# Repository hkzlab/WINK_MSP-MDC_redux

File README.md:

# MSP-MDC Redux

## DISCLAIMER

Any use of this project is **under your own responsibility**.
You will be responsible of checking the correct construction and functionality of your board.
By using this project You will agree that I cannot be held responsible if it will destroy any of your devices, damage your computer, burn down your house or whatever.

## Introduction

Wink is a 1985, breakout-style, arcade game by Midcoin.

The game uses off-the-shelf components for everything, but a bunch of circuitry, called the MSP-MDC module, that acts both as CPU and as 
security (scrambling addresses accessed by the CPU), is placed on 3 sandwiched PCBs encased in epoxy.
This was made to thwart bootleggers, but if something within this epoxied block dies, the whole game stops working.

I painstakingly pulled the block apart and chipped away the epoxy to recover the schematic.

This project contains files to build a compatible board that can be plugged in place of the original MSP-MDC.

## Hardware

The board was designed with [KiCad](https://kicad.org/) EDA.

You can order boards directly from [PCBWay](https://www.pcbway.com/project/shareproject/MSP_MDC_Redux_c4e8a048.html)!

### Bill of Materials

| Component         | Qty | Type / Value                   | Notes                                                    |
| ----------------- | --- | ------------------------------ | -------------------------------------------------------- |
| C1 - C14          | 19  | 100nF / 1206 / ceramic         |                                                          |
| R1, R2            |  2  | 1K / 1206                      |                                                          |
| RN1               |  1  | 9-pin bussed 10K resistor array|                                                          |
|                   |  4  | 4x15pin 2.54mm straight headers| Mount on the 4 sides of the module                       |
| U2                |  1  | DIP-40 Z80A CPU                | It's a good idea to socket this                          |
| U3, U14           |  2  | 74LS374 SO-20                  | 5.3x12.6mm                                               |
| U4                |  1  | 74ALS00 SOIC-14                | 3.9x8.7mm                                                |
| U5                |  1  | 74ALS32 SOIC-14                | 3.9x8.7mm                                                |
| U6                |  1  | 74LS245 SO-20                  | 5.3x12.6mm                                               |
| U7                |  1  | 74ALS244 SO-20                 | 5.3x12.6mm                                               |
| U8, U20           |  2  | 74LS283 SOIC-16                | 3.9x9.9mm                                                |
| U10               |  1  | 74LS00 SOIC-14                 | 3.9x8.7mm                                                |
| U11               |  1  | 74LS32 SOIC-14                 | 3.9x8.7mm                                                |
| U12               |  1  | 74LS86 SOIC-14                 | 3.9x8.7mm                                                |
| U13               |  1  | 74LS166 SOIC-16                | 3.9x9.9mm                                                |
| U15               |  1  | 74LS138 SOIC-16                | 3.9x9.9mm                                                |
| U16 - U19         |  4  | 74LS257 SOIC-16                | 3.9x9.9mm                                                |

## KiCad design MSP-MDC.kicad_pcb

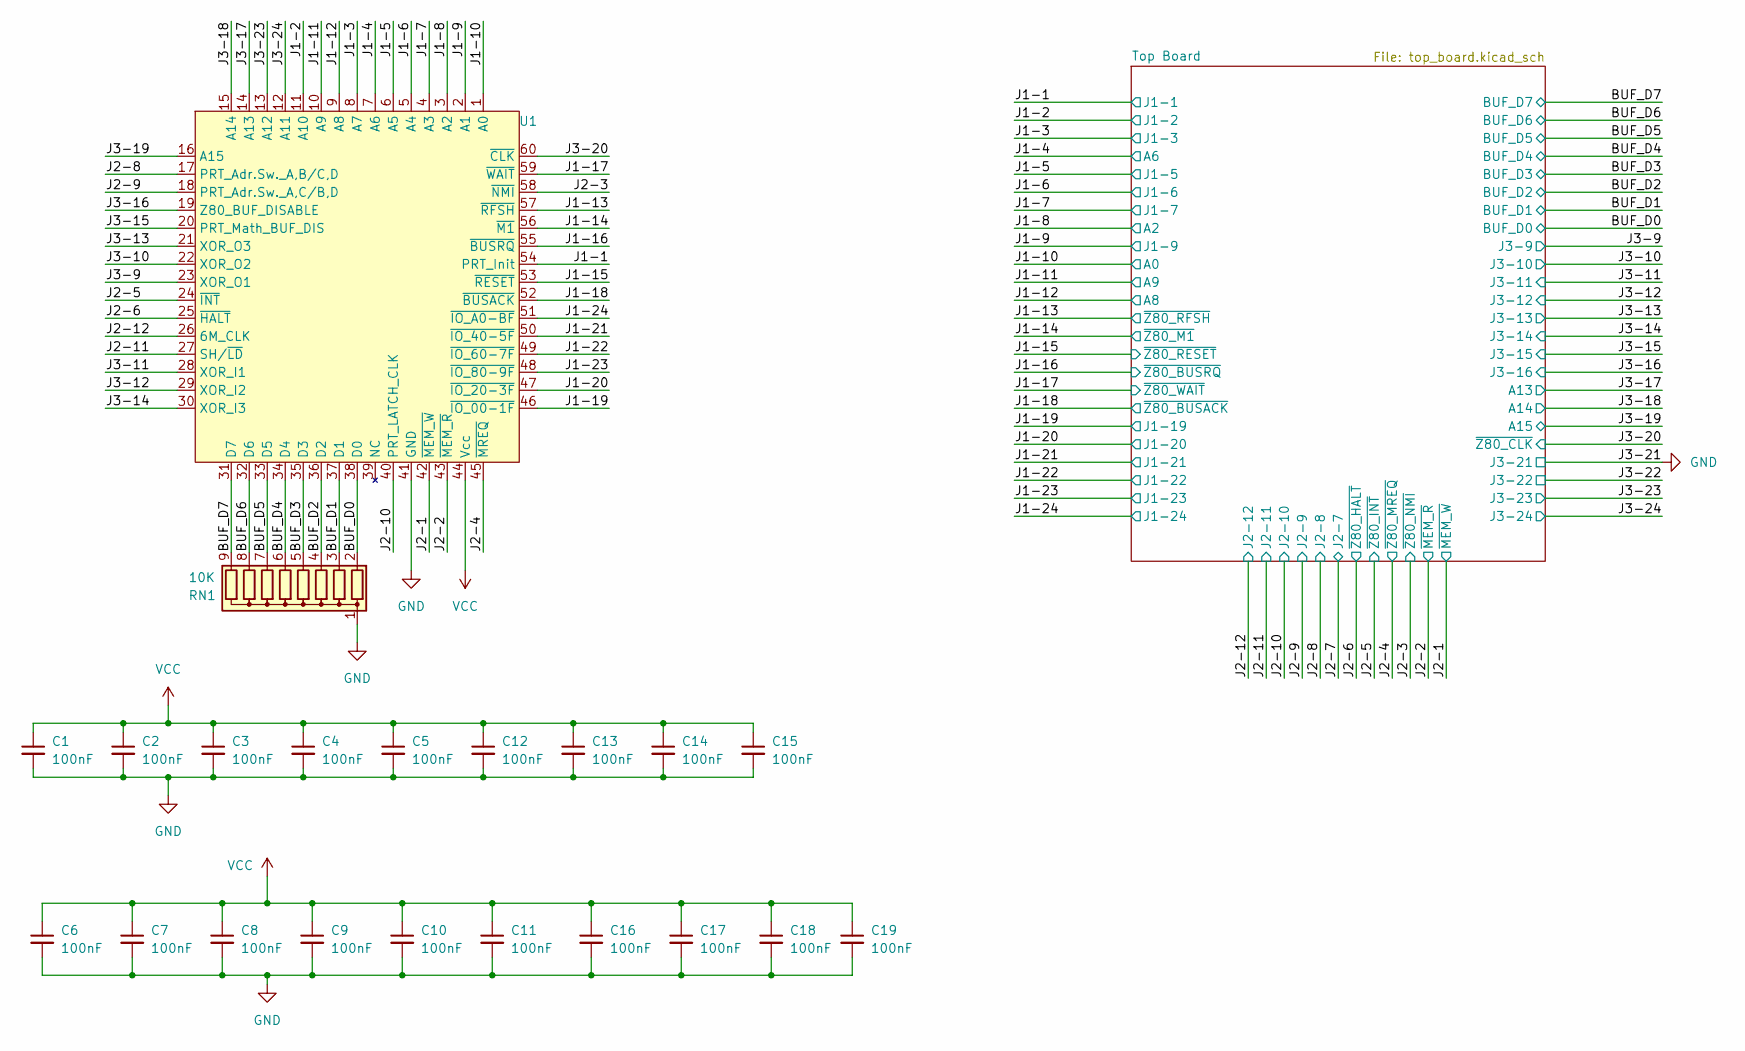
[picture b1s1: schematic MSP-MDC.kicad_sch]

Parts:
C1, C2, C3, C4, C5, C6, C7, C8, C9, C10, C11, C12, C13, C14, C15, C16, C17, C18, C19: 100nF; C_1206_3216Metric_Pad1.33x1.80mm_HandSolder
RN1: 10K; R_Array_SIP9
U1: MSP-MDC

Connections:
/BUF_D0: RN1.2 (R1), U1.38 (D0); also elsewhere on the board
/BUF_D1: RN1.3 (R2), U1.37 (D1); also elsewhere on the board
/BUF_D2: RN1.4 (R3), U1.36 (D2); also elsewhere on the board
/BUF_D3: RN1.5 (R4), U1.35 (D3); also elsewhere on the board
/BUF_D4: RN1.6 (R5), U1.34 (D4); also elsewhere on the board
/BUF_D5: RN1.7 (R6), U1.33 (D5); also elsewhere on the board
/BUF_D6: RN1.8 (R7), U1.32 (D6); also elsewhere on the board
/BUF_D7: RN1.9 (R8), U1.31 (D7); also elsewhere on the board
/J1-1: U1.54 (PRT_Init); also elsewhere on the board
/J1-2: U1.11 (A10); also elsewhere on the board
/J1-3: U1.8 (A7); also elsewhere on the board
/J1-4: U1.7 (A6); also elsewhere on the board
/J1-5: U1.6 (A5); also elsewhere on the board
/J1-6: U1.5 (A4); also elsewhere on the board
/J1-7: U1.4 (A3); also elsewhere on the board
/J1-8: U1.3 (A2); also elsewhere on the board
/J1-9: U1.2 (A1); also elsewhere on the board
/J1-10: U1.1 (A0); also elsewhere on the board
/J1-11: U1.10 (A9); also elsewhere on the board
/J1-12: U1.9 (A8); also elsewhere on the board
/J1-13: U1.57 (~RFSH); also elsewhere on the board
/J1-14: U1.56 (~M1); also elsewhere on the board
/J1-15: U1.53 (~RESET); also elsewhere on the board
/J1-16: U1.55 (~BUSRQ); also elsewhere on the board
/J1-17: U1.59 (~WAIT); also elsewhere on the board
/J1-18: U1.52 (~BUSACK); also elsewhere on the board
/J1-19: U1.46 (~IO_00-1F); also elsewhere on the board
/J1-20: U1.47 (~IO_20-3F); also elsewhere on the board
/J1-21: U1.50 (~IO_40-5F); also elsewhere on the board
/J1-22: U1.49 (~IO_60-7F); also elsewhere on the board
/J1-23: U1.48 (~IO_80-9F); also elsewhere on the board
/J1-24: U1.51 (~IO_A0-BF); also elsewhere on the board
/J2-1: U1.42 (~MEM_W); also elsewhere on the board
/J2-2: U1.43 (~MEM_R); also elsewhere on the board
/J2-3: U1.58 (~NMI); also elsewhere on the board
/J2-4: U1.45 (~MREQ); also elsewhere on the board
/J2-5: U1.24 (~INT); also elsewhere on the board
/J2-6: U1.25 (~HALT); also elsewhere on the board
/J2-8: U1.17 (PRT_Adr.Sw._A,B/C,D); also elsewhere on the board
/J2-9: U1.18 (PRT_Adr.Sw._A,C/B,D); also elsewhere on the board
/J2-10: U1.40 (PRT_LATCH_CLK); also elsewhere on the board
/J2-11: U1.27 (SH/~LD); also elsewhere on the board
/J2-12: U1.26 (6M_CLK); also elsewhere on the board
/J3-9: U1.23 (XOR_O1); also elsewhere on the board
/J3-10: U1.22 (XOR_O2); also elsewhere on the board
/J3-11: U1.28 (XOR_I1); also elsewhere on the board
/J3-12: U1.29 (XOR_I2); also elsewhere on the board
/J3-13: U1.21 (XOR_O3); also elsewhere on the board
/J3-14: U1.30 (XOR_I3); also elsewhere on the board
/J3-15: U1.20 (PRT_Math_BUF_DIS); also elsewhere on the board
/J3-16: U1.19 (Z80_BUF_DISABLE); also elsewhere on the board
/J3-17: U1.14 (A13); also elsewhere on the board
/J3-18: U1.15 (A14); also elsewhere on the board
/J3-19: U1.16 (A15); also elsewhere on the board
/J3-20: U1.60 (~CLK); also elsewhere on the board
/J3-23: U1.13 (A12); also elsewhere on the board
/J3-24: U1.12 (A11); also elsewhere on the board
GND: C1.2, C2.2, C3.2, C4.2, C5.2, C6.2, C7.2, C8.2, C9.2, C10.2, C11.2, C12.2, C13.2, C14.2, C15.2, C16.2, C17.2, C18.2, C19.2, RN1.1 (common), U1.41 (GND); also elsewhere on the board
VCC: C1.1, C2.1, C3.1, C4.1, C5.1, C6.1, C7.1, C8.1, C9.1, C10.1, C11.1, C12.1, C13.1, C14.1, C15.1, C16.1, C17.1, C18.1, C19.1, U1.44 (Vcc); also elsewhere on the board

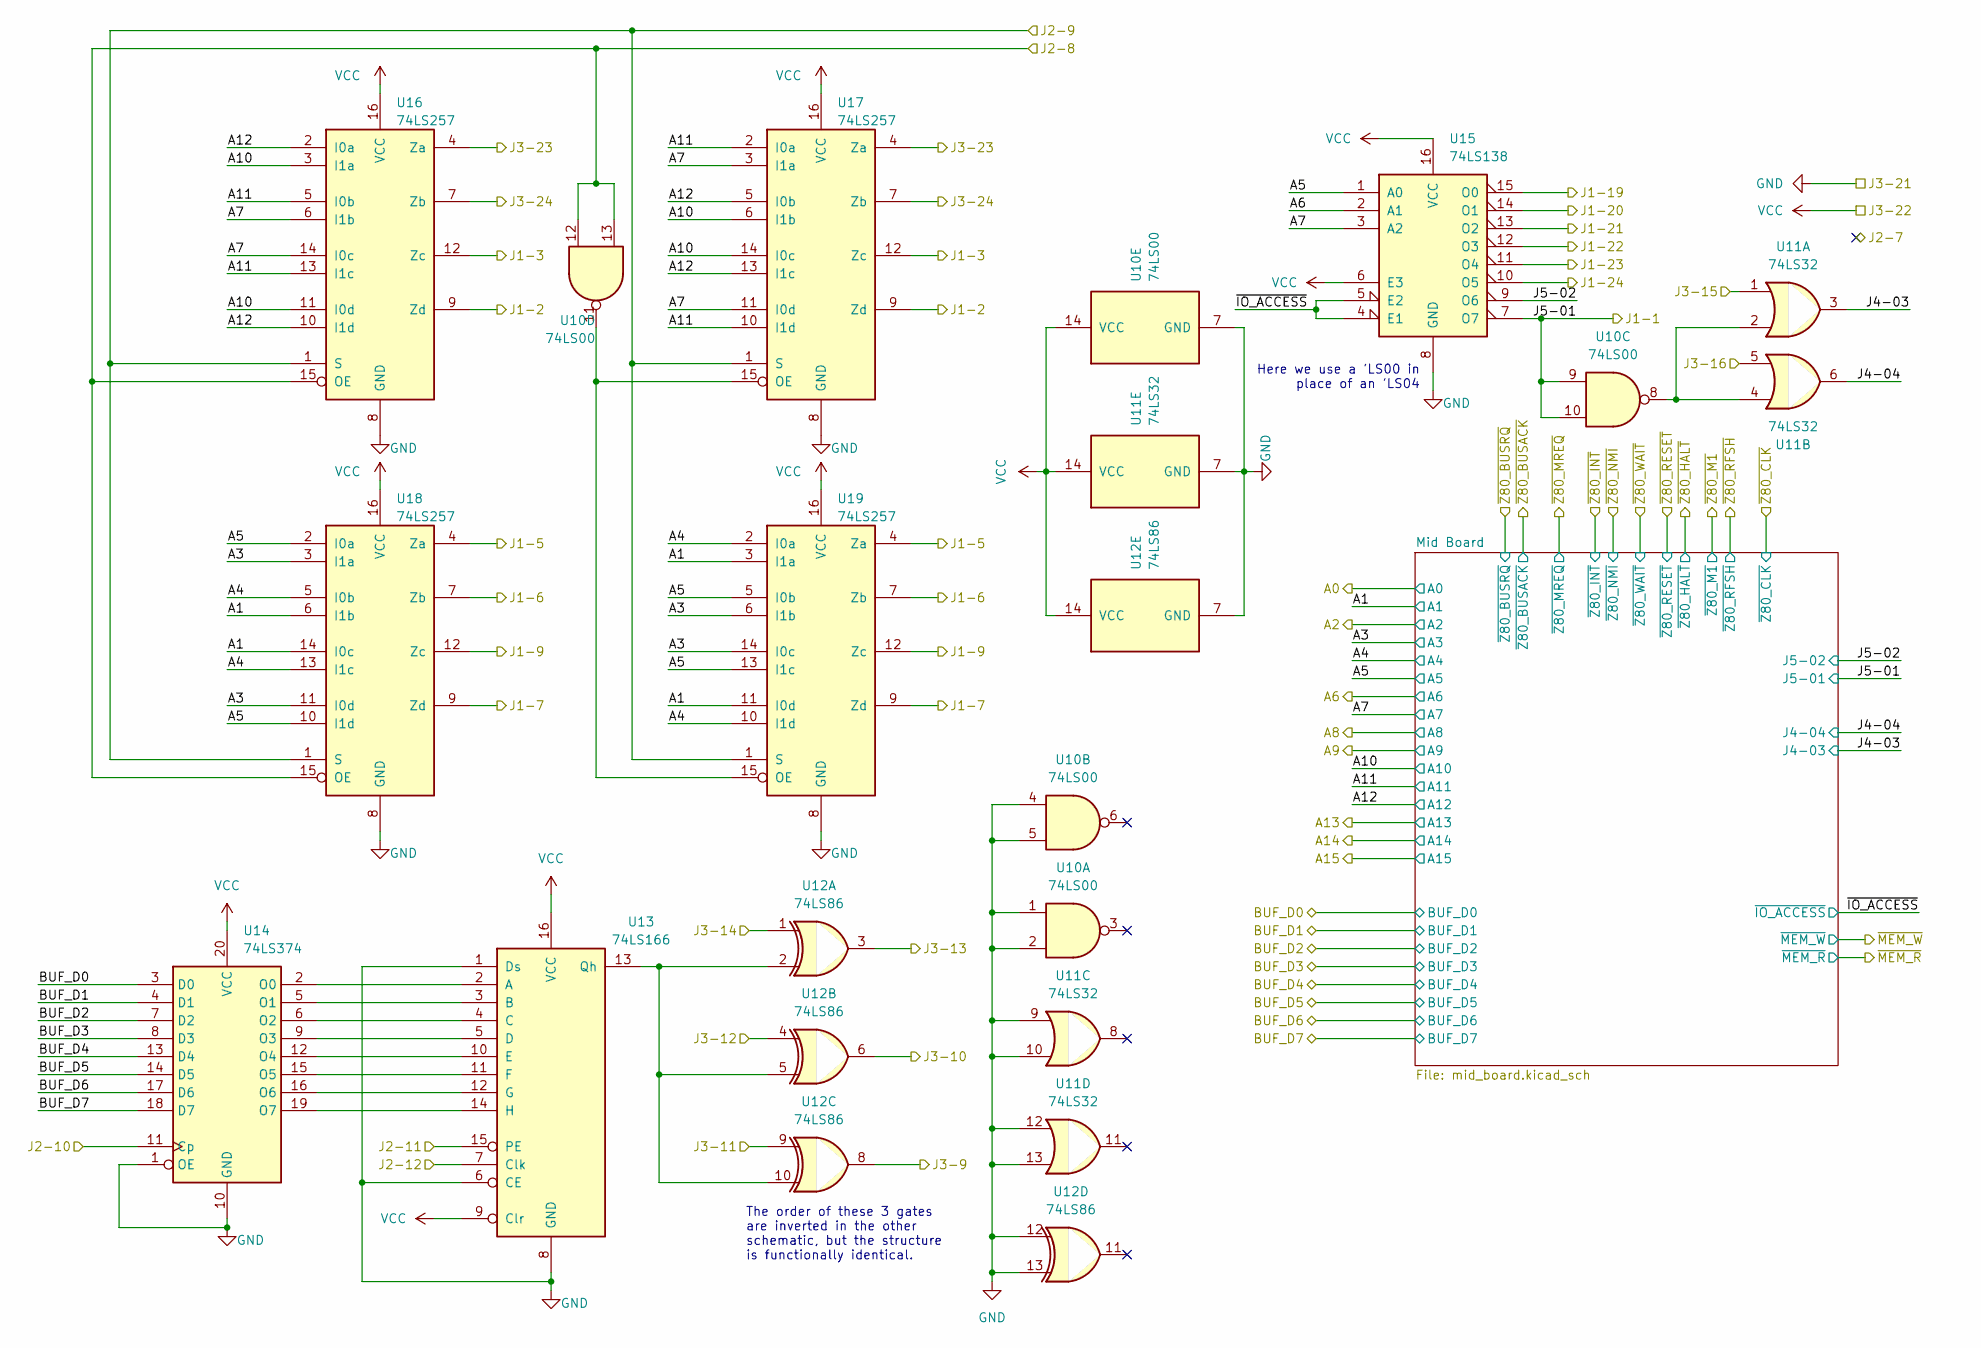
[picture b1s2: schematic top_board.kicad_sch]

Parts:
U10: 74LS00; SOIC-14_3.9x8.7mm_P1.27mm
U11: 74LS32; SOIC-14_3.9x8.7mm_P1.27mm
U12: 74LS86; SOIC-14_3.9x8.7mm_P1.27mm
U13: 74LS166; SOIC-16_3.9x9.9mm_P1.27mm
U14: 74LS374; SO-20_5.3x12.6mm_P1.27mm
U15: 74LS138; SOIC-16_3.9x9.9mm_P1.27mm
U16, U17, U18, U19: 74LS257; SOIC-16_3.9x9.9mm_P1.27mm

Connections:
/BUF_D0: U14.3 (D0); also elsewhere on the board
/BUF_D1: U14.4 (D1); also elsewhere on the board
/BUF_D2: U14.7 (D2); also elsewhere on the board
/BUF_D3: U14.8 (D3); also elsewhere on the board
/BUF_D4: U14.13 (D4); also elsewhere on the board
/BUF_D5: U14.14 (D5); also elsewhere on the board
/BUF_D6: U14.17 (D6); also elsewhere on the board
/BUF_D7: U14.18 (D7); also elsewhere on the board
/J1-1: U10.9, U10.10, U15.7 (O7); also elsewhere on the board
/J1-2: U16.9 (Zd), U17.9 (Zd); also elsewhere on the board
/J1-3: U16.12 (Zc), U17.12 (Zc); also elsewhere on the board
/J1-4: U15.2 (A1); also elsewhere on the board
/J1-5: U18.4 (Za), U19.4 (Za); also elsewhere on the board
/J1-6: U18.7 (Zb), U19.7 (Zb); also elsewhere on the board
/J1-7: U18.9 (Zd), U19.9 (Zd); also elsewhere on the board
/J1-9: U18.12 (Zc), U19.12 (Zc); also elsewhere on the board
/J1-19: U15.15 (O0); also elsewhere on the board
/J1-20: U15.14 (O1); also elsewhere on the board
/J1-21: U15.13 (O2); also elsewhere on the board
/J1-22: U15.12 (O3); also elsewhere on the board
/J1-23: U15.11 (O4); also elsewhere on the board
/J1-24: U15.10 (O5); also elsewhere on the board
/J2-8: U10.12, U10.13, U16.15 (OE), U18.15 (OE); also elsewhere on the board
/J2-9: U16.1 (S), U17.1 (S), U18.1 (S), U19.1 (S); also elsewhere on the board
/J2-10: U14.11 (Cp); also elsewhere on the board
/J2-11: U13.15 (PE); also elsewhere on the board
/J2-12: U13.7 (Clk); also elsewhere on the board
/J3-9: U12.8; also elsewhere on the board
/J3-10: U12.6; also elsewhere on the board
/J3-11: U12.9; also elsewhere on the board
/J3-12: U12.4; also elsewhere on the board
/J3-13: U12.3; also elsewhere on the board
/J3-14: U12.1; also elsewhere on the board
/J3-15: U11.1; also elsewhere on the board
/J3-16: U11.5; also elsewhere on the board
/J3-23: U16.4 (Za), U17.4 (Za); also elsewhere on the board
/J3-24: U16.7 (Zb), U17.7 (Zb); also elsewhere on the board
/Top Board/A1: U18.6 (I1b), U18.14 (I0c), U19.3 (I1a), U19.11 (I0d); also elsewhere on the board
/Top Board/A3: U18.3 (I1a), U18.11 (I0d), U19.6 (I1b), U19.14 (I0c); also elsewhere on the board
/Top Board/A4: U18.5 (I0b), U18.13 (I1c), U19.2 (I0a), U19.10 (I1d); also elsewhere on the board
/Top Board/A5: U15.1 (A0), U18.2 (I0a), U18.10 (I1d), U19.5 (I0b), U19.13 (I1c); also elsewhere on the board
/Top Board/A7: U15.3 (A2), U16.6 (I1b), U16.14 (I0c), U17.3 (I1a), U17.11 (I0d); also elsewhere on the board
/Top Board/A10: U16.3 (I1a), U16.11 (I0d), U17.6 (I1b), U17.14 (I0c); also elsewhere on the board
/Top Board/A11: U16.5 (I0b), U16.13 (I1c), U17.2 (I0a), U17.10 (I1d); also elsewhere on the board
/Top Board/A12: U16.2 (I0a), U16.10 (I1d), U17.5 (I0b), U17.13 (I1c); also elsewhere on the board
/Top Board/J4-03: U11.3; also elsewhere on the board
/Top Board/J4-04: U11.6; also elsewhere on the board
/Top Board/J5-02: U15.9 (O6); also elsewhere on the board
/Top Board/~IO_ACCESS: U15.4 (E1), U15.5 (E2); also elsewhere on the board
GND: U10.1, U10.2, U10.4, U10.5, U10.7 (GND), U11.7 (GND), U11.9, U11.10, U11.12, U11.13, U12.7 (GND), U12.12, U12.13, U13.1 (Ds), U13.6 (CE), U13.8 (GND), U14.1 (OE), U14.10 (GND), U15.8 (GND), U16.8 (GND), U17.8 (GND), U18.8 (GND), U19.8 (GND); also elsewhere on the board
unnamed: U10.8, U11.2, U11.4
unnamed: U13.2 (A), U14.2 (O0)
unnamed: U13.3 (B), U14.5 (O1)
unnamed: U13.4 (C), U14.6 (O2)
unnamed: U13.5 (D), U14.9 (O3)
unnamed: U13.10 (E), U14.12 (O4)
unnamed: U13.11 (F), U14.15 (O5)
unnamed: U13.12 (G), U14.16 (O6)
unnamed: U13.14 (H), U14.19 (O7)
unnamed: U12.2, U12.5, U12.10, U13.13 (Qh)
unnamed: U10.11, U17.15 (OE), U19.15 (OE)
VCC: U10.14 (VCC), U11.14 (VCC), U12.14 (VCC), U13.9 (Clr), U13.16 (VCC), U14.20 (VCC), U15.6 (E3), U15.16 (VCC), U16.16 (VCC), U17.16 (VCC), U18.16 (VCC), U19.16 (VCC); also elsewhere on the board

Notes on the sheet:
The order of these 3 gates are inverted in the other schematic, but the structure is functionally identical.
Here we use a 'LS00 in place of an 'LS04

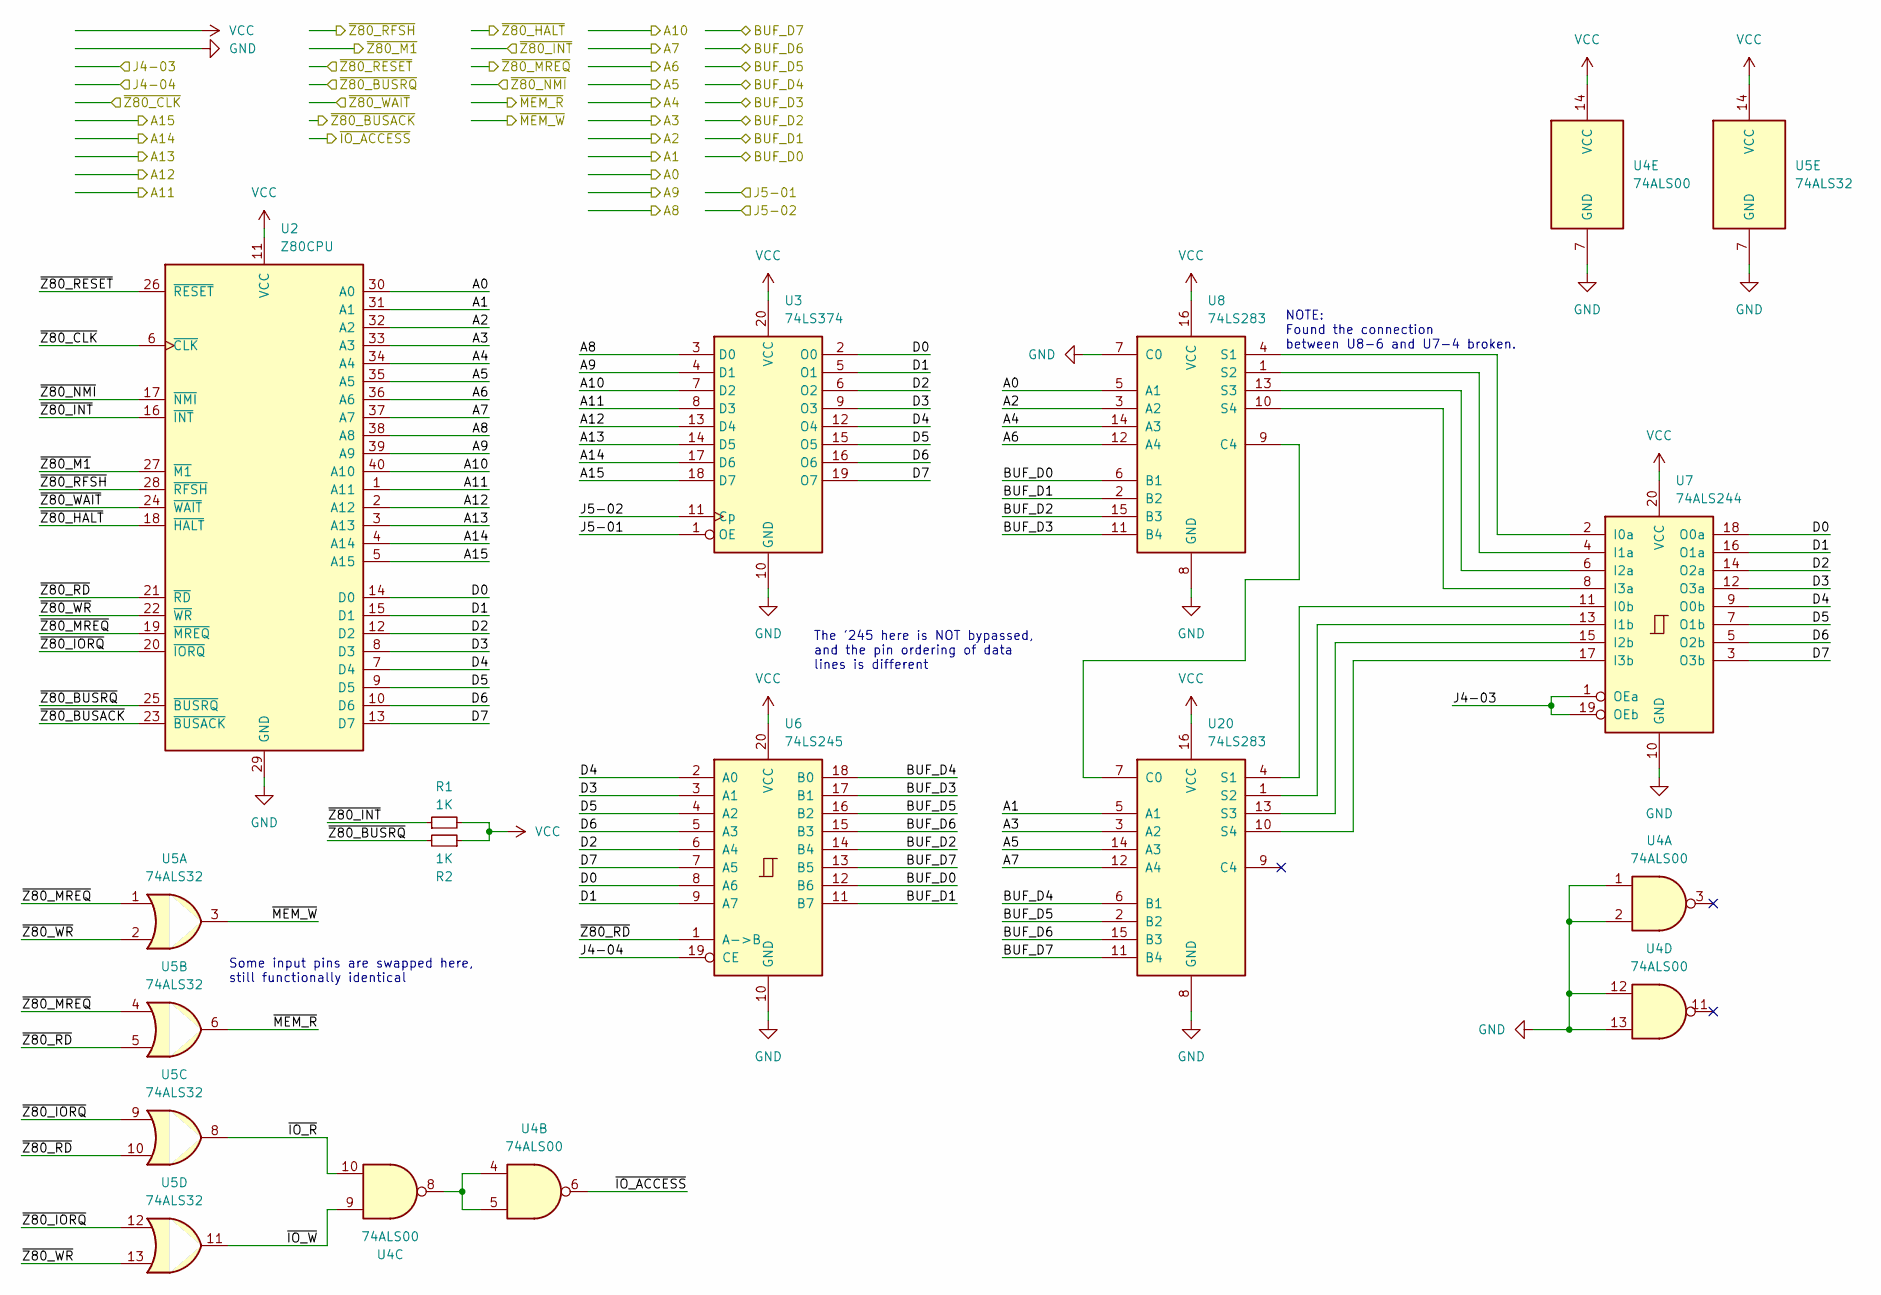
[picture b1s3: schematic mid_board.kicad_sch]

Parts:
R1, R2: 1K; R_1206_3216Metric_Pad1.30x1.75mm_HandSolder
U2: Z80CPU; DIP-40_W15.24mm_Socket
U3: 74LS374; SO-20_5.3x12.6mm_P1.27mm
U4: 74ALS00; SOIC-14_3.9x8.7mm_P1.27mm
U5: 74ALS32; SOIC-14_3.9x8.7mm_P1.27mm
U6: 74LS245; SO-20_5.3x12.6mm_P1.27mm
U7: 74ALS244; SO-20_5.3x12.6mm_P1.27mm
U8, U20: 74LS283; SOIC-16_3.9x9.9mm_P1.27mm

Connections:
/BUF_D0: U6.12 (B6), U8.6 (B1); also elsewhere on the board
/BUF_D1: U6.11 (B7), U8.2 (B2); also elsewhere on the board
/BUF_D2: U6.14 (B4), U8.15 (B3); also elsewhere on the board
/BUF_D3: U6.17 (B1), U8.11 (B4); also elsewhere on the board
/BUF_D4: U6.18 (B0), U20.6 (B1); also elsewhere on the board
/BUF_D5: U6.16 (B2), U20.2 (B2); also elsewhere on the board
/BUF_D6: U6.15 (B3), U20.15 (B3); also elsewhere on the board
/BUF_D7: U6.13 (B5), U20.11 (B4); also elsewhere on the board
/J1-1: U3.1 (OE); also elsewhere on the board
/J1-4: U2.36 (A6), U8.12 (A4); also elsewhere on the board
/J1-8: U2.32 (A2), U8.3 (A2); also elsewhere on the board
/J1-10: U2.30 (A0), U8.5 (A1); also elsewhere on the board
/J1-11: U2.39 (A9), U3.4 (D1); also elsewhere on the board
/J1-12: U2.38 (A8), U3.3 (D0); also elsewhere on the board
/J1-13: U2.28 (~RFSH); also elsewhere on the board
/J1-14: U2.27 (~M1); also elsewhere on the board
/J1-15: U2.26 (~RESET); also elsewhere on the board
/J1-16: R2.2, U2.25 (~BUSRQ); also elsewhere on the board
/J1-17: U2.24 (~WAIT); also elsewhere on the board
/J1-18: U2.23 (~BUSACK); also elsewhere on the board
/J2-1: U5.3; also elsewhere on the board
/J2-2: U5.6; also elsewhere on the board
/J2-3: U2.17 (~NMI); also elsewhere on the board
/J2-4: U2.19 (~MREQ), U5.1, U5.4; also elsewhere on the board
/J2-5: R1.1, U2.16 (~INT); also elsewhere on the board
/J2-6: U2.18 (~HALT); also elsewhere on the board
/J3-17: U2.3 (A13), U3.14 (D5); also elsewhere on the board
/J3-18: U2.4 (A14), U3.17 (D6); also elsewhere on the board
/J3-19: U2.5 (A15), U3.18 (D7); also elsewhere on the board
/J3-20: U2.6 (~CLK); also elsewhere on the board
/Top Board/A1: U2.31 (A1), U20.5 (A1); also elsewhere on the board
/Top Board/A3: U2.33 (A3), U20.3 (A2); also elsewhere on the board
/Top Board/A4: U2.34 (A4), U8.14 (A3); also elsewhere on the board
/Top Board/A5: U2.35 (A5), U20.14 (A3); also elsewhere on the board
/Top Board/A7: U2.37 (A7), U20.12 (A4); also elsewhere on the board
/Top Board/A10: U2.40 (A10), U3.7 (D2); also elsewhere on the board
/Top Board/A11: U2.1 (A11), U3.8 (D3); also elsewhere on the board
/Top Board/A12: U2.2 (A12), U3.13 (D4); also elsewhere on the board
/Top Board/J4-03: U7.1 (OEa), U7.19 (OEb); also elsewhere on the board
/Top Board/J4-04: U6.19 (CE); also elsewhere on the board
/Top Board/J5-02: U3.11 (Cp); also elsewhere on the board
/Top Board/Mid Board/D0: U2.14 (D0), U3.2 (O0), U6.8 (A6), U7.18 (O0a)
/Top Board/Mid Board/D1: U2.15 (D1), U3.5 (O1), U6.9 (A7), U7.16 (O1a)
/Top Board/Mid Board/D2: U2.12 (D2), U3.6 (O2), U6.6 (A4), U7.14 (O2a)
/Top Board/Mid Board/D3: U2.8 (D3), U3.9 (O3), U6.3 (A1), U7.12 (O3a)
/Top Board/Mid Board/D4: U2.7 (D4), U3.12 (O4), U6.2 (A0), U7.9 (O0b)
/Top Board/Mid Board/D5: U2.9 (D5), U3.15 (O5), U6.4 (A2), U7.7 (O1b)
/Top Board/Mid Board/D6: U2.10 (D6), U3.16 (O6), U6.5 (A3), U7.5 (O2b)
/Top Board/Mid Board/D7: U2.13 (D7), U3.19 (O7), U6.7 (A5), U7.3 (O3b)
/Top Board/Mid Board/~IO_R: U4.10, U5.8
/Top Board/Mid Board/~IO_W: U4.9, U5.11
/Top Board/Mid Board/~Z80_IORQ: U2.20 (~IORQ), U5.9, U5.12
/Top Board/Mid Board/~Z80_RD: U2.21 (~RD), U5.5, U5.10, U6.1 (A->B)
/Top Board/Mid Board/~Z80_WR: U2.22 (~WR), U5.2, U5.13
/Top Board/~IO_ACCESS: U4.6; also elsewhere on the board
GND: U2.29 (GND), U3.10 (GND), U4.1, U4.2, U4.7 (GND), U4.12, U4.13, U5.7 (GND), U6.10 (GND), U7.10 (GND), U8.7 (C0), U8.8 (GND), U20.8 (GND); also elsewhere on the board
unnamed: U4.4, U4.5, U4.8
unnamed: U7.2 (I0a), U8.4 (S1)
unnamed: U7.4 (I1a), U8.1 (S2)
unnamed: U7.6 (I2a), U8.13 (S3)
unnamed: U7.8 (I3a), U8.10 (S4)
unnamed: U8.9 (C4), U20.7 (C0)
unnamed: U7.11 (I0b), U20.4 (S1)
unnamed: U7.13 (I1b), U20.1 (S2)
unnamed: U7.15 (I2b), U20.13 (S3)
unnamed: U7.17 (I3b), U20.10 (S4)
VCC: R1.2, R2.1, U2.11 (VCC), U3.20 (VCC), U4.14 (VCC), U5.14 (VCC), U6.20 (VCC), U7.20 (VCC), U8.16 (VCC), U20.16 (VCC); also elsewhere on the board

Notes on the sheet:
The '245 here is NOT bypassed, and the pin ordering of data lines is different
Some input pins are swapped here, still functionally identical
NOTE: Found the connection between U8-6 and U7-4 broken.

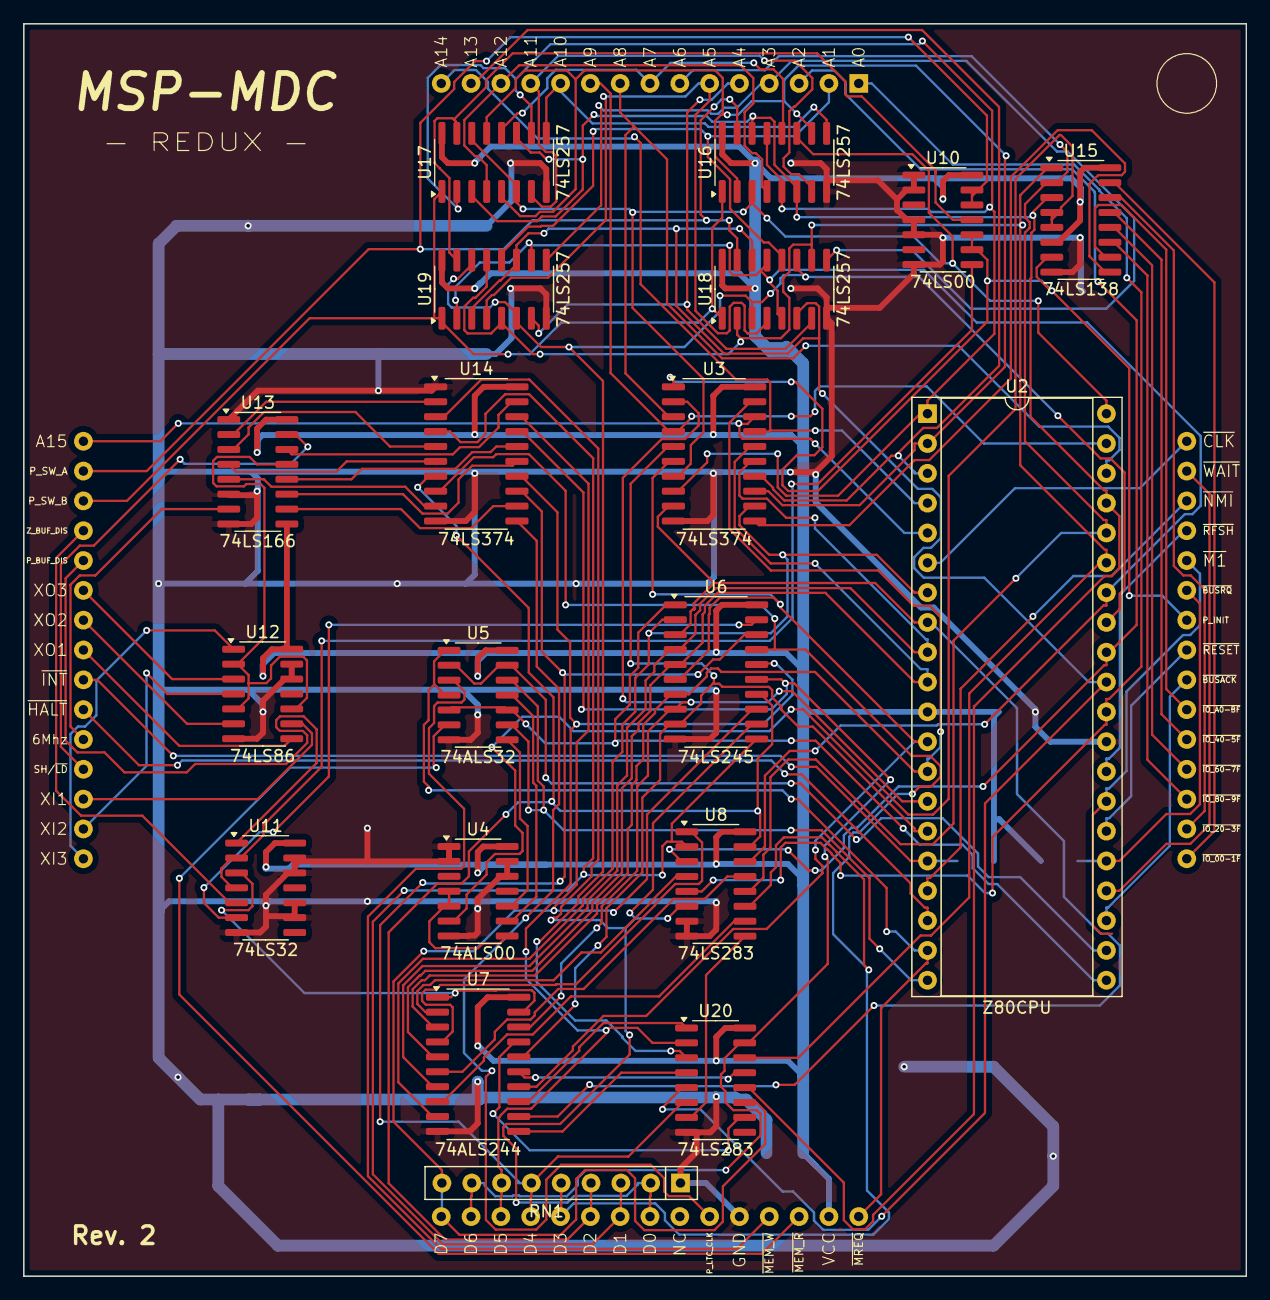
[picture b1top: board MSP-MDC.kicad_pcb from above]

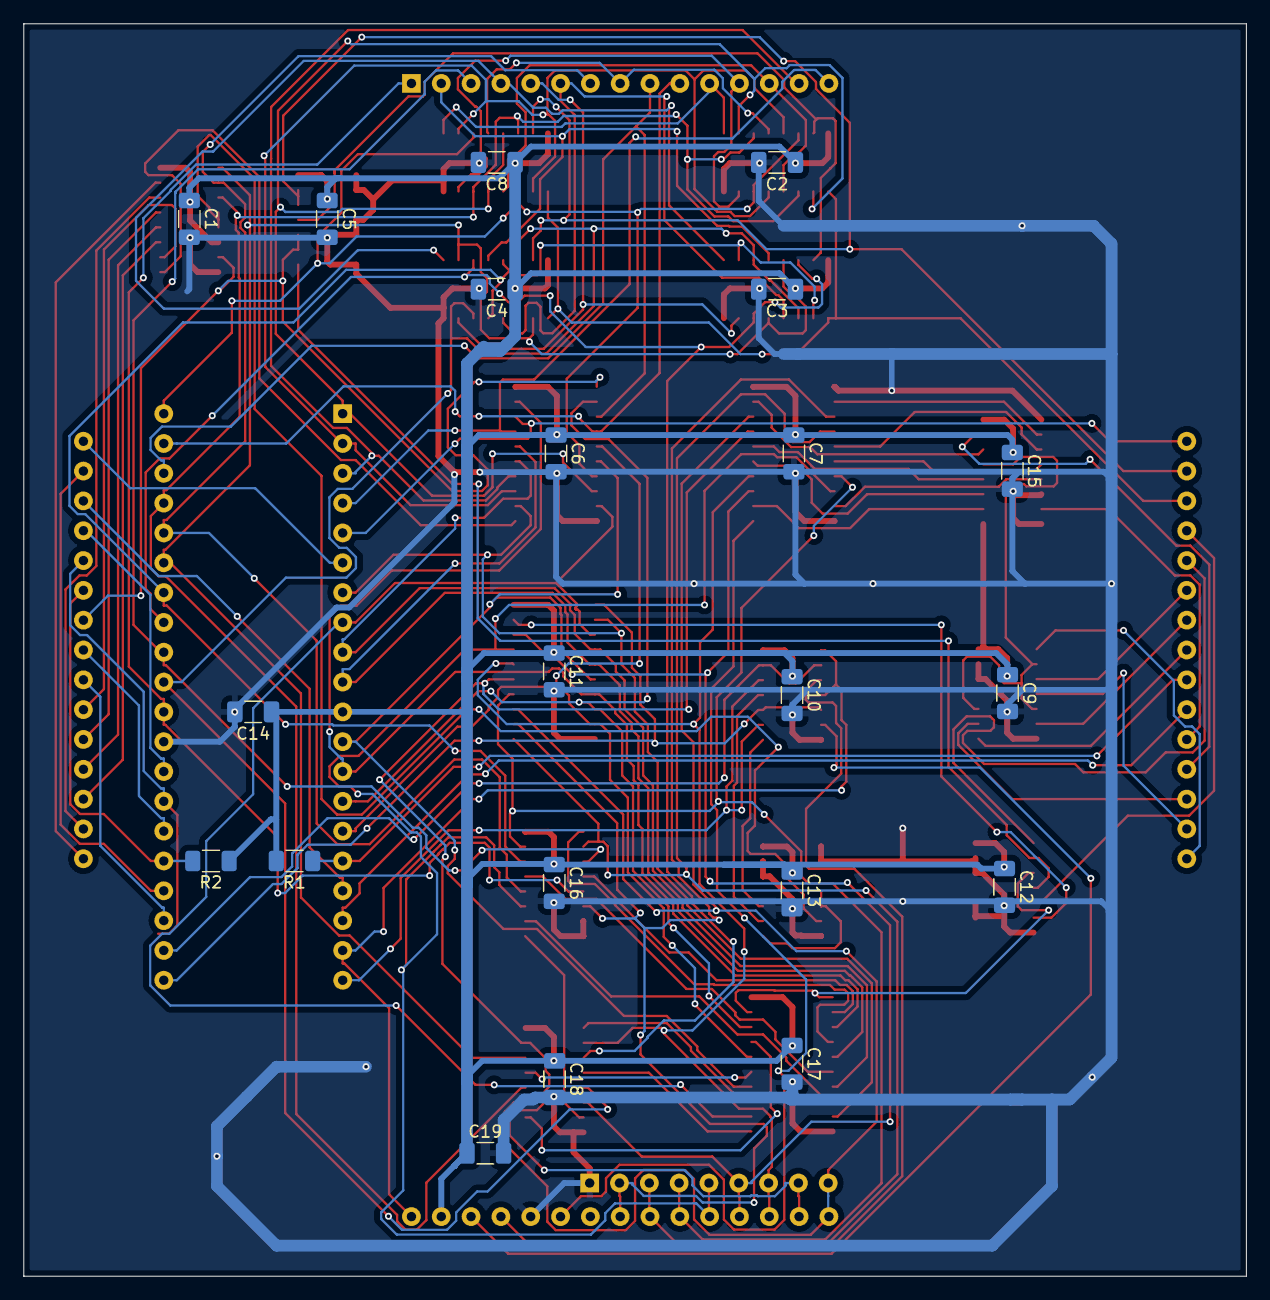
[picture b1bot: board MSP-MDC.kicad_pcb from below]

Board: 2 copper layers, 104.1 x 106.7 mm, 41 parts (21 on the bottom side), 105 nets.

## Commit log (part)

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2024-07-28 import msp-mdc project
2024-07-28 Added some basic traces for power
2024-07-28 Import routing for the first revision
2024-08-07 Reduce size of the board to match original
2024-08-07 Resize the board
2024-08-09 Fix adder bit ordering
2024-08-09 Update board fixing adder issues
2024-08-21 Removed some text from schematic, added some more, generate PDF
2024-08-21 Fill in the README
2024-08-21 Add pic
2024-08-21 Mention PCBWay, update the readme
2024-08-21 More details in README
2024-08-22 Fix some wording in README
